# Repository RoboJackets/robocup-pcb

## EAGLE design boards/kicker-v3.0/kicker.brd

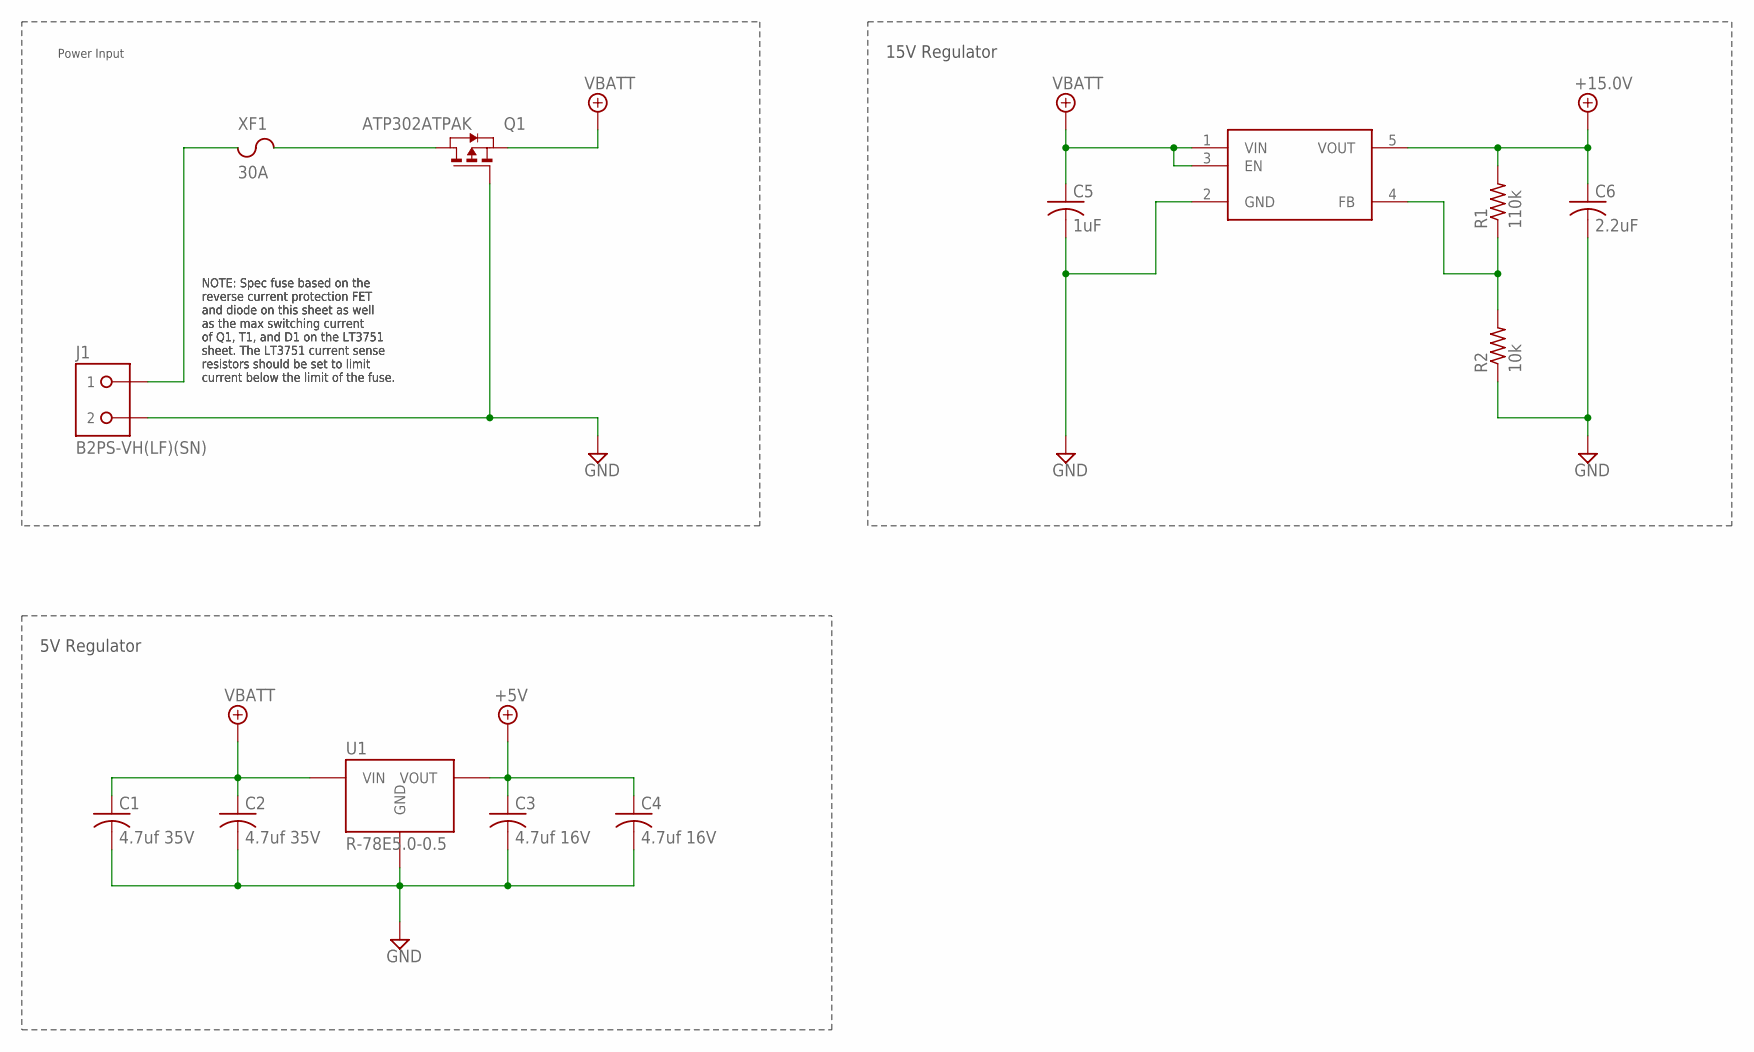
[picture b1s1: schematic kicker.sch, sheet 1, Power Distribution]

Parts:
C1, C2: 4.7uf 35V; C1210
C3, C4: 4.7uf 16V; C1210
C5: 1uF; C0603
C6: 2.2uF; C0603
J1: B2PS-VH(LF)(SN); B2PS-CENTERED
Q1: ATP302ATPAK; TO460P950X150-3
R1: 110k; R0603
R2: 10k; R0603
U1: R-78E5.0-0.5; R-78E
U2: 15V; SOT95P280X145-5
XF1: 30A; 3557-2

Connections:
+5V: C3.1, C4.1, U1.3 (VOUT); also elsewhere on the board
+15.0V: C6.1, R1.2, U2.5 (VOUT); also elsewhere on the board
GND: C1.2, C2.2, C3.2, C4.2, C5.2, C6.2, J1.2, Q1.1 (G), R2.1, U1.2 (GND), U2.2 (GND); also elsewhere on the board
unnamed: Q1.3 (D), XF1.3 (2), XF1.4 (2)
unnamed: R1.1, R2.2, U2.4 (FB)
unnamed: J1.1, XF1.1, XF1.2 (1)
VBATT: C1.1, C2.1, C5.1, Q1.2 (S), U1.1 (VIN), U2.1 (VIN), U2.3 (EN); also elsewhere on the board

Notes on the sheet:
Power Input
5V Regulator
NOTE: Spec fuse based on the reverse current protection FET and diode on this sheet as well as the max switching current of Q1, T1, and D1 on the LT3751 sheet. The LT3751 current sense resistors should be set to limit current below the limit of the fuse.
15V Regulator

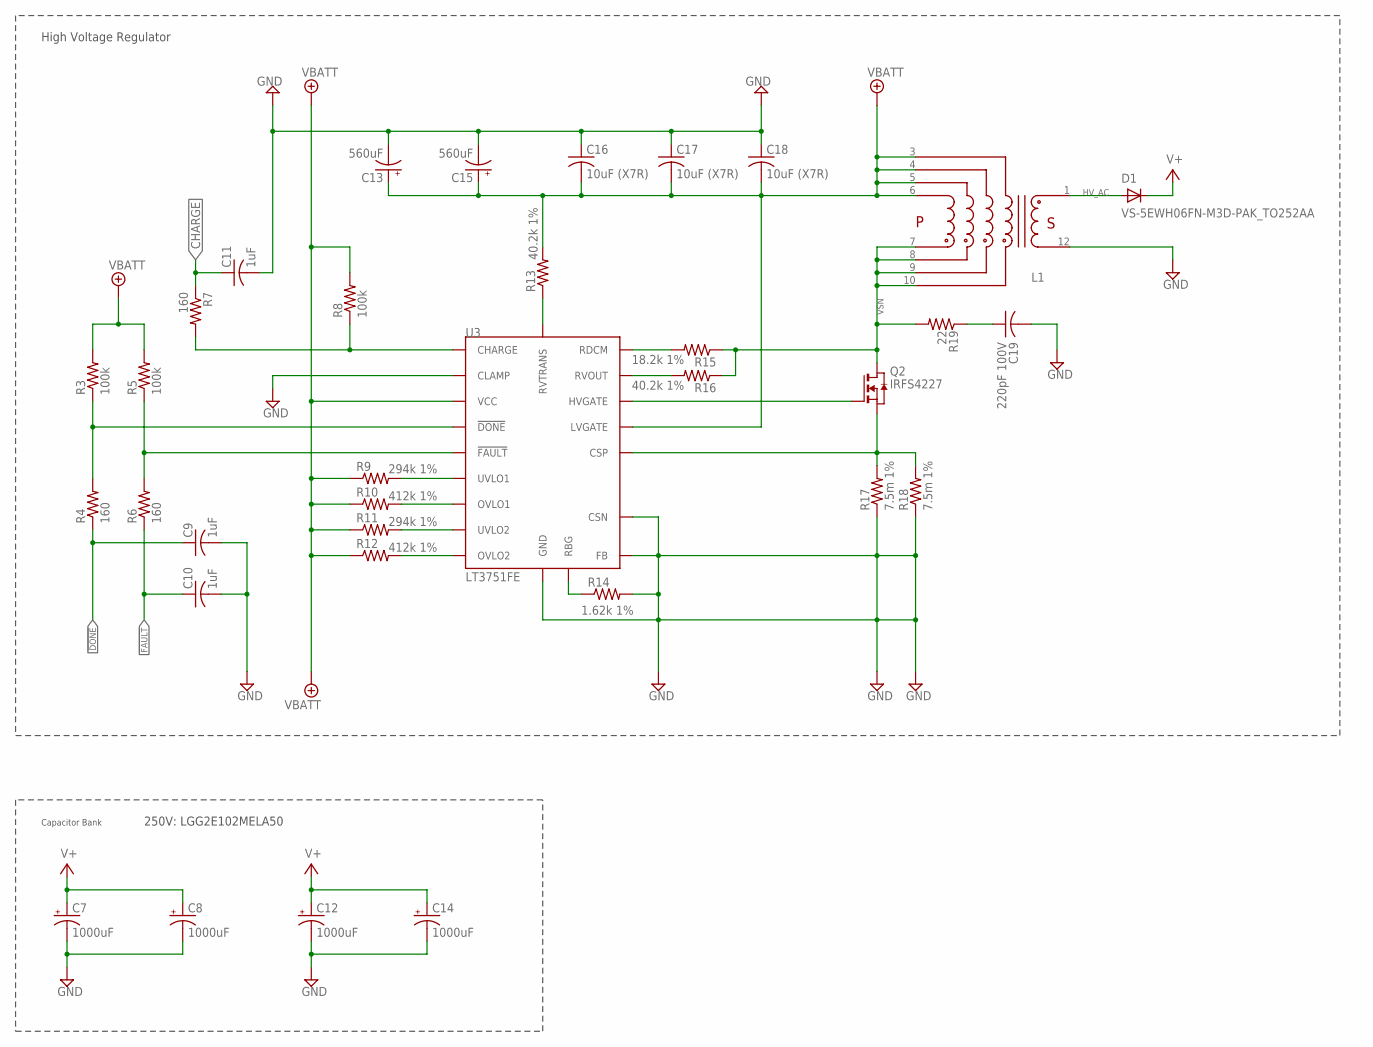
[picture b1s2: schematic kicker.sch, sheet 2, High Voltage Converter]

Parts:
C7, C8, C12, C14: 1000uF; EB25D
C9, C10, C11: 1uF; C0603
C13, C15: 560uF; E7,5-18
C16, C17, C18: 10uF (X7R); C1210
C19: 220pF 100V; C0603
D1: VS-5EWH06FN-M3D-PAK_TO252AA; TO460P990X239-3
L1: GA34XX-BLBL; SOP400P3370X1400-12
Q2: IRFS4227; D2PAK
R3, R5, R8: 100k; R0603
R4, R6, R7: 160; R0603
R9, R11: 294k 1%; R0805
R10, R12: 412k 1%; R0805
R13, R16: 40.2k 1%; R0805
R14: 1.62k 1%; R0805
R15: 18.2k 1%; R0805
R17, R18: 7.5m 1%; R2512
R19: 22; R0805
U3: LT3751FE; TSSOP-20_EP

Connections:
!DONE!: C9.1, R4.1; also elsewhere on the board
!DONE_LPF: R3.1, R4.2, U3.7 (!DONE); also elsewhere on the board
!FAULT!: C10.1, R6.1; also elsewhere on the board
!FAULT_LPF: R5.1, R6.2, U3.6 (!FAULT); also elsewhere on the board
CHARGE: C11.1, R7.1; also elsewhere on the board
CHARGE_LPF: R7.2, R8.1, U3.8 (CHARGE)
GND: C7.-, C8.-, C9.2, C10.2, C11.2, C12.-, C13.-, C14.-, C15.-, C16.1, C17.1, C18.1, C19.2, L1.12, R14.2, R17.1, R18.1, U3.9 (CLAMP), U3.10 (FB), U3.11 (CSN), U3.PAD (GND); also elsewhere on the board
HVGATE: Q2.1 (G), U3.15 (HVGATE)
HV_AC: D1.2 (A), L1.1
unnamed: R14.1, U3.16 (RBG)
unnamed: R13.1, U3.1 (RVTRANS)
unnamed: C19.1, R19.1
OVLO1: R10.2, U3.3 (OVLO1)
OVLO2: R12.2, U3.5 (OVLO2)
RDCM: R15.2, U3.20 (RDCM)
RVOUT: R16.2, U3.18 (RVOUT)
SENSE: Q2.3 (S), R17.2, R18.2, U3.12 (CSP)
UVLO1: R9.2, U3.2 (UVLO1)
UVLO2: R11.2, U3.4 (UVLO2)
V+: C7.+, C8.+, C12.+, C14.+, D1.3 (C); also elsewhere on the board
VBATT: C13.+, C15.+, C16.2, C17.2, C18.2, L1.3, L1.4, L1.5, L1.6, R3.2, R5.2, R8.2, R9.1, R10.1, R11.1, R12.1, R13.2, U3.13 (VCC), U3.14 (LVGATE); also elsewhere on the board
VSN: L1.7, L1.8, L1.9, L1.10, Q2.2 (D), R15.1, R16.1, R19.2

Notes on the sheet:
Capacitor Bank
High Voltage Regulator
250V: LGG2E102MELA50

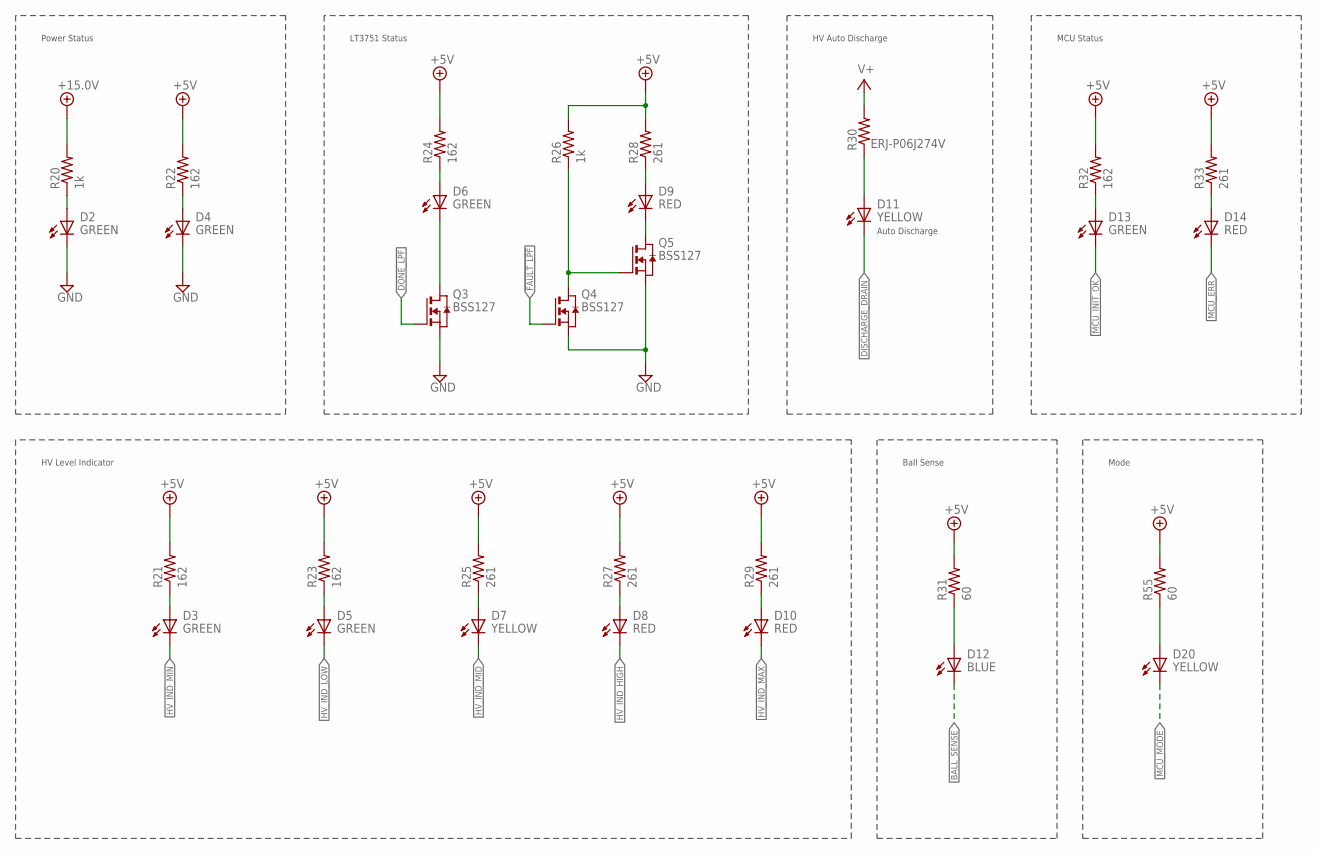
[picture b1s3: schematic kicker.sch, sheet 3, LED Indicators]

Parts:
D2, D3, D4, D5, D6, D13: GREEN; CHIP-LED0603
D7, D11, D20: YELLOW; CHIP-LED0603
D8, D9, D10, D14: RED; CHIP-LED0603
D12: BLUE; CHIP-LED0603
Q3, Q4, Q5: BSS127; SOT-23-3
R20, R26: 1k; R0603
R21, R22, R23, R24, R32: 162; R0603
R25, R27, R28, R29, R33: 261; R0603
R30: ERJ-P06J274V; R0805
R31, R55: 60; R0603

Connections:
!DONE_LPF: Q3.1 (G); also elsewhere on the board
!FAULT_LPF: Q4.1 (G); also elsewhere on the board
+5V: R21.2, R22.2, R23.2, R24.2, R25.2, R26.2, R27.2, R28.2, R29.2, R31.2, R32.2, R33.2, R55.2; also elsewhere on the board
+15.0V: R20.2; also elsewhere on the board
BALL_SENSE: D12.C (K); also elsewhere on the board
DISCHARGE_DRAIN: D11.C (K); also elsewhere on the board
GND: D2.C (K), D4.C (K), Q3.2 (S), Q4.2 (S), Q5.2 (S); also elsewhere on the board
HV_IND_HIGH: D8.C (K); also elsewhere on the board
HV_IND_LOW: D5.C (K); also elsewhere on the board
HV_IND_MAX: D10.C (K); also elsewhere on the board
HV_IND_MID: D7.C (K); also elsewhere on the board
HV_IND_MIN: D3.C (K); also elsewhere on the board
MCU_ERR: D14.C (K); also elsewhere on the board
MCU_INIT_OK: D13.C (K); also elsewhere on the board
MCU_MODE: D20.C (K); also elsewhere on the board
unnamed: D14.A, R33.1
unnamed: D13.A, R32.1
unnamed: D6.A, R24.1
unnamed: D3.A, R21.1
unnamed: D5.A, R23.1
unnamed: D7.A, R25.1
unnamed: D20.A, R55.1
unnamed: D4.A, R22.1
unnamed: D8.A, R27.1
unnamed: D2.A, R20.1
unnamed: Q4.3 (D), Q5.1 (G), R26.1
unnamed: D9.A, R28.1
unnamed: D9.C (K), Q5.3 (D)
unnamed: D11.A, R30.1
unnamed: D10.A, R29.1
unnamed: D6.C (K), Q3.3 (D)
unnamed: D12.A, R31.1
V+: R30.2; also elsewhere on the board

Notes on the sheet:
Power Status
LT3751 Status
Auto Discharge
HV Auto Discharge
MCU Status
HV Level Indicator
Ball Sense
Mode

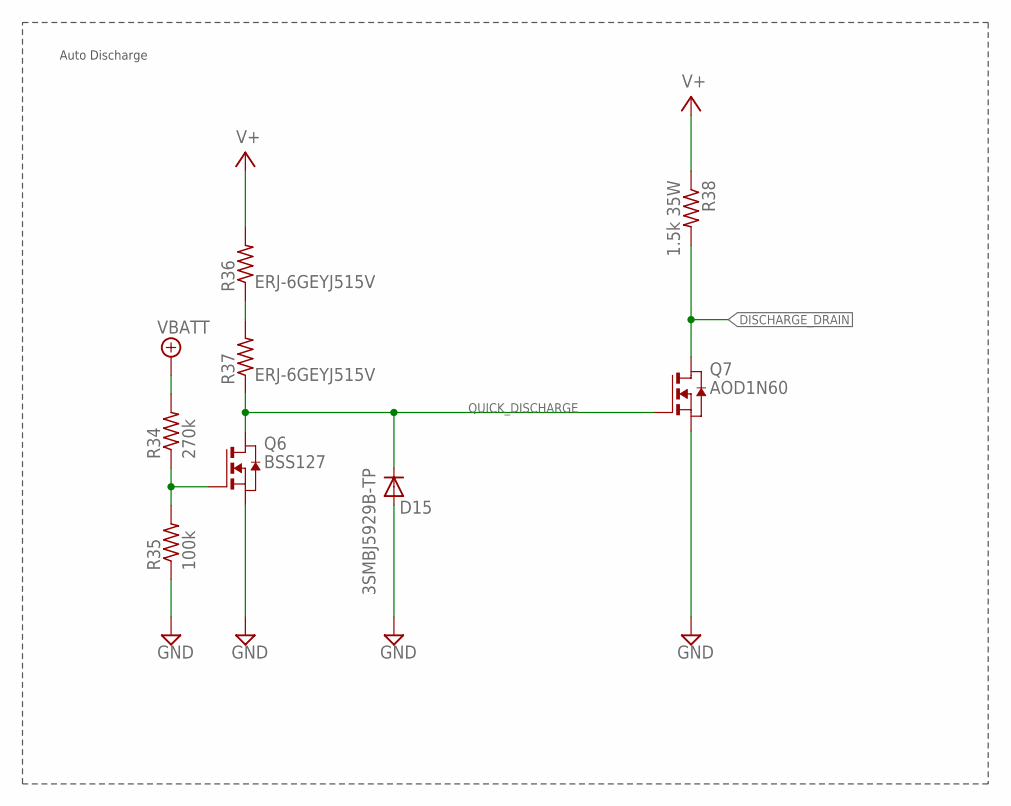
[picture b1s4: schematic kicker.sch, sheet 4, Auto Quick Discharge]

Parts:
D15: 3SMBJ5929B-TP; DO214AA
Q6: BSS127; SOT-23-3
Q7: AOD1N60; DPAK
R34: 270k; R0603
R35: 100k; R0603
R36, R37: ERJ-6GEYJ515V; R0805
R38: 1.5k 35W; TO508P1539X450-3

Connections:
DISCHARGE_DRAIN: Q7.FIN (D), R38.2 (PIN2); also elsewhere on the board
GND: D15.A, Q6.2 (S), Q7.3 (S), R35.1; also elsewhere on the board
unnamed: R36.1, R37.2
unnamed: Q6.1 (G), R34.1, R35.2
QUICK_DISCHARGE: D15.C, Q6.3 (D), Q7.1 (G), R37.1
V+: R36.2, R38.1 (PIN1); also elsewhere on the board
VBATT: R34.2; also elsewhere on the board

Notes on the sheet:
Auto Discharge

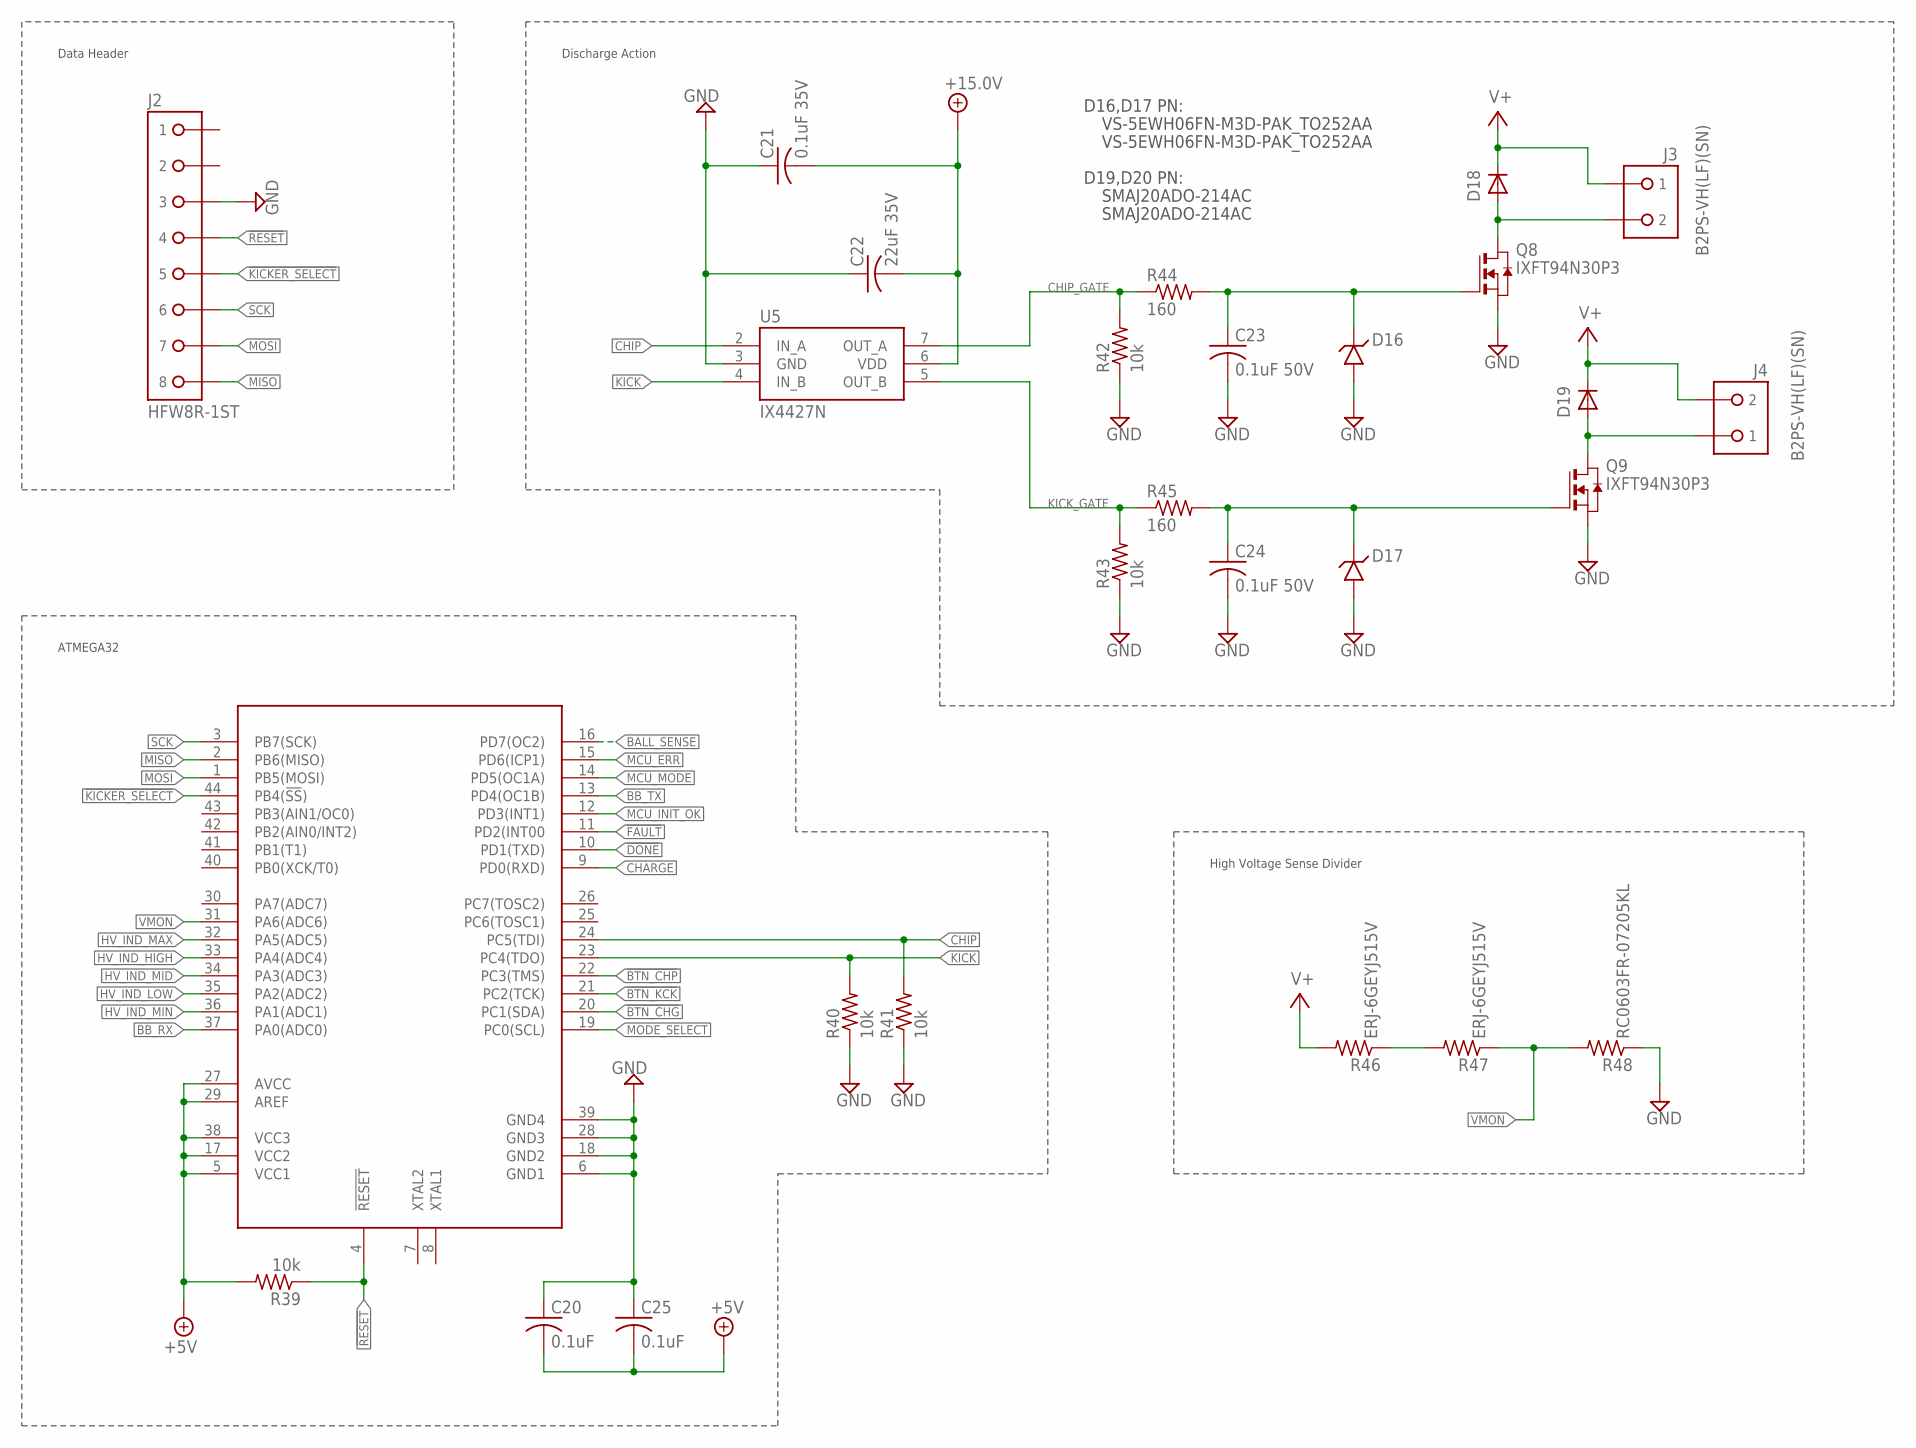
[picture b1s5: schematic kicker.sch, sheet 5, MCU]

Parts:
C20, C25: 0.1uF; C0603
C21: 0.1uF 35V; C0603
C22: 22uF 35V; C0805
C23, C24: 0.1uF 50V; C0603
D16, D17: SMAJ20ADO-214AC; RESM5226X262
D18, D19: VS-5EWH06FN-M3D-PAK_TO252AA; TO460P990X239-3
J2: HFW8R-1ST
J3, J4: B2PS-VH(LF)(SN); B2PS-CENTERED
Q8, Q9: IXFT94N30P3; TO-268
R39, R40, R41, R42, R43: 10k; R0603
R44, R45: 160; R1206
R46, R47: ERJ-6GEYJ515V; R0805
R48: RC0603FR-07205KL; R0603
U4: AT32ATQFP44; QFP80P1200X1200X120-44
U5: IX4427N; SOIC-8

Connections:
!BTN_CHG: U4.20 (PC1(SDA)); also elsewhere on the board
!BTN_CHP: U4.22 (PC3(TMS)); also elsewhere on the board
!BTN_KCK: U4.21 (PC2(TCK)); also elsewhere on the board
!DONE!: U4.10 (PD1(TXD)); also elsewhere on the board
!FAULT!: U4.11 (PD2(INT00); also elsewhere on the board
!KICKER_SELECT: J2.5, U4.44 (PB4(!SS!))
!RESET: J2.4, R39.1, U4.4 (!RESET!)
+5V: C20.2, C25.2, R39.2, U4.5 (VCC1), U4.17 (VCC2), U4.27 (AVCC), U4.29 (AREF), U4.38 (VCC3); also elsewhere on the board
+15.0V: C21.2, C22.2, U5.6 (VDD); also elsewhere on the board
BALL_SENSE: U4.16 (PD7(OC2)); also elsewhere on the board
BB_RX: U4.37 (PA0(ADC0)); also elsewhere on the board
BB_TX: U4.13 (PD4(OC1B)); also elsewhere on the board
CHARGE: U4.9 (PD0(RXD)); also elsewhere on the board
CHIP: R41.2, U4.24 (PC5(TDI)), U5.2 (IN_A)
CHIPPER: D18.2 (A), J3.2, Q8.4 (D)
CHIP_GATE: R42.2, R44.1, U5.7 (OUT_A)
GND: C20.1, C21.1, C22.1, C23.2, C24.2, C25.1, D16.1 (A), D17.1 (A), J2.3, Q8.3 (S), Q9.3 (S), R40.1, R41.1, R42.1, R43.1, R48.1, U4.6 (GND1), U4.18 (GND2), U4.28 (GND3), U4.39 (GND4), U5.3 (GND); also elsewhere on the board
HV_IND_HIGH: U4.33 (PA4(ADC4)); also elsewhere on the board
HV_IND_LOW: U4.35 (PA2(ADC2)); also elsewhere on the board
HV_IND_MAX: U4.32 (PA5(ADC5)); also elsewhere on the board
HV_IND_MID: U4.34 (PA3(ADC3)); also elsewhere on the board
HV_IND_MIN: U4.36 (PA1(ADC1)); also elsewhere on the board
KICK: R40.2, U4.23 (PC4(TDO)), U5.4 (IN_B)
KICKER: D19.2 (A), J4.1, Q9.4 (D)
KICK_GATE: R43.2, R45.1, U5.5 (OUT_B)
MCU_ERR: U4.15 (PD6(ICP1)); also elsewhere on the board
MCU_INIT_OK: U4.12 (PD3(INT1)); also elsewhere on the board
MCU_MODE: U4.14 (PD5(OC1A)); also elsewhere on the board
MISO: J2.8, U4.2 (PB6(MISO))
MODE_SELECT: U4.19 (PC0(SCL)); also elsewhere on the board
MOSI: J2.7, U4.1 (PB5(MOSI))
unnamed: C23.1, D16.2 (C), Q8.1 (G), R44.2
unnamed: C24.1, D17.2 (C), Q9.1 (G), R45.2
unnamed: R46.1, R47.2
SCK: J2.6, U4.3 (PB7(SCK))
V+: D18.3 (C), D19.3 (C), J3.1, J4.2, R46.2; also elsewhere on the board
VMON: R47.1, R48.2, U4.31 (PA6(ADC6))

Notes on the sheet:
ATMEGA32
Data Header
Discharge Action
High Voltage Sense Divider
D16,D17 PN:
D19,D20 PN:
VS-5EWH06FN-M3D-PAK_TO252AA
SMAJ20ADO-214AC

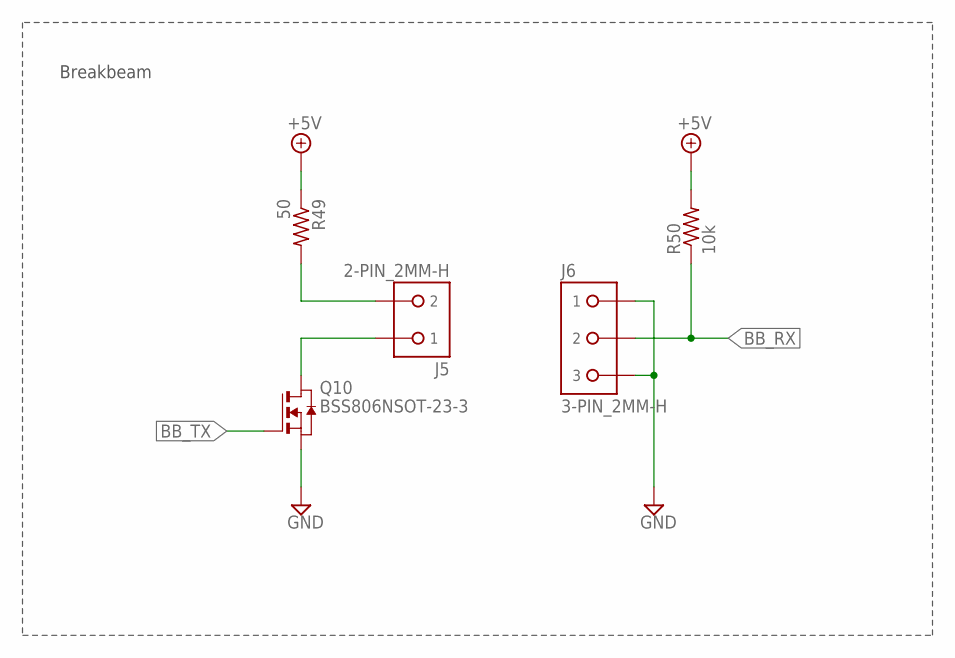
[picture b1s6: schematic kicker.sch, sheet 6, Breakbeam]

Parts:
J5: 2-PIN_2MM-H; 2MM-2-H
J6: 3-PIN_2MM-H; 2MM-3-H
Q10: BSS806NSOT-23-3; SOT95P240X110-3
R49: 50; R0603
R50: 10k; R0603

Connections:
+5V: R49.1, R50.2; also elsewhere on the board
BB_RX: J6.2, R50.1; also elsewhere on the board
BB_TX: Q10.1 (G); also elsewhere on the board
GND: J6.1, J6.3, Q10.2 (S); also elsewhere on the board
unnamed: J5.2, R49.2
unnamed: J5.1, Q10.3 (D)

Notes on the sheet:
Breakbeam

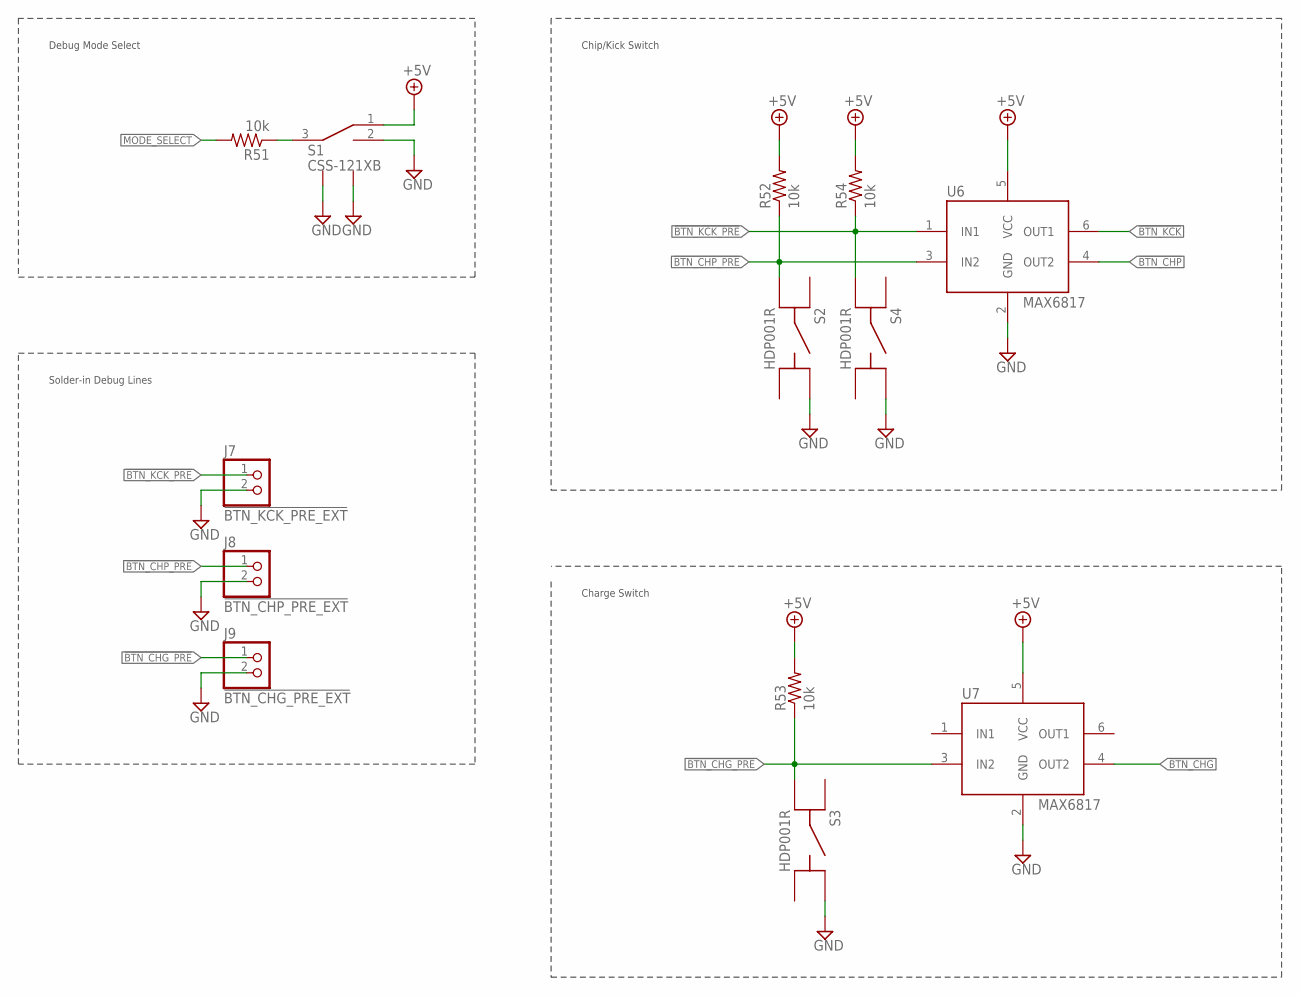
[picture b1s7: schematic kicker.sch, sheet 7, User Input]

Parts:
J7: !BTN_KCK_PRE_EXT; 1X2
J8: !BTN_CHP_PRE_EXT; 1X2
J9: !BTN_CHG_PRE_EXT; 1X2
R51, R52, R53, R54: 10k; R0603
S1: CSS-121XB
S2, S3, S4: HDP001R
U6, U7: MAX6817; SOT-23-6

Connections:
!BTN_CHG: U7.4 (OUT2); also elsewhere on the board
!BTN_CHG_PRE: J9.1, R53.1, S3.C (A2), U7.3 (IN2)
!BTN_CHP: U6.4 (OUT2); also elsewhere on the board
!BTN_CHP_PRE: J8.1, R52.1, S2.C (A2), U6.3 (IN2)
!BTN_KCK: U6.6 (OUT1); also elsewhere on the board
!BTN_KCK_PRE: J7.1, R54.1, S4.C (A2), U6.1 (IN1)
+5V: R52.2, R53.2, R54.2, S1.1 (A), U6.5 (VCC), U7.5 (VCC); also elsewhere on the board
GND: J7.2, J8.2, J9.2, S1.2 (B), S1.LEG1, S1.LEG4 (LEG2), S2.B (B1), S3.B (B1), S4.B (B1), U6.2 (GND), U7.2 (GND); also elsewhere on the board
MODE_SELECT: R51.2; also elsewhere on the board
unnamed: R51.1, S1.3 (COMMON)

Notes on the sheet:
Debug Mode Select
Chip/Kick Switch
Charge Switch
Solder-in Debug Lines

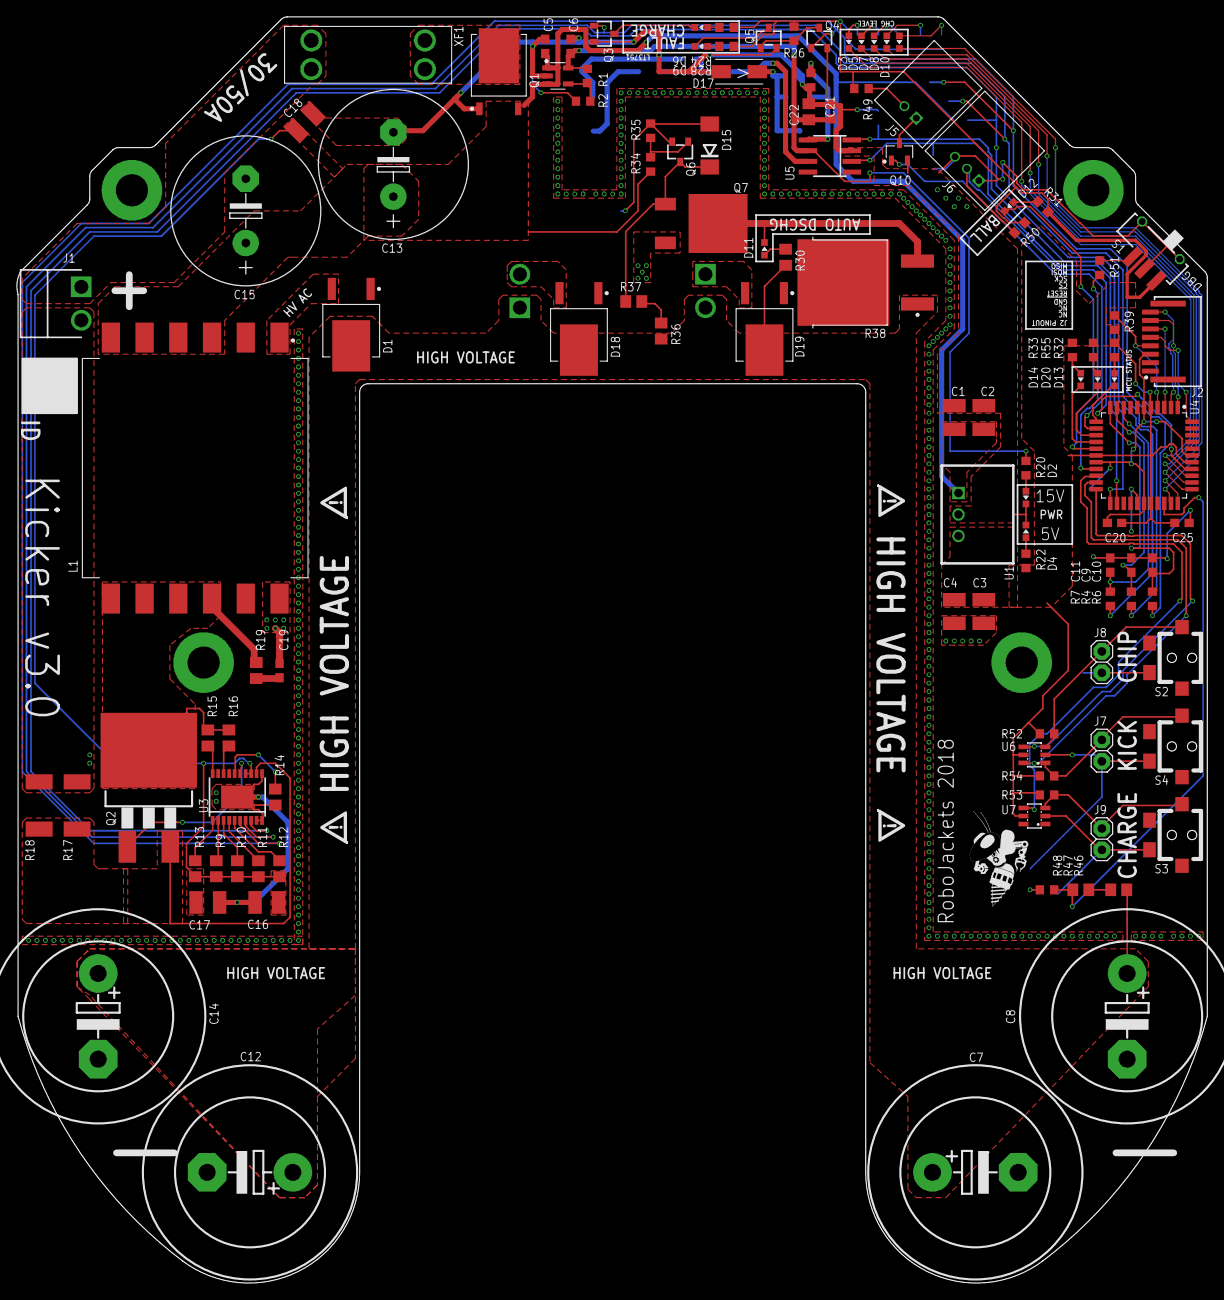
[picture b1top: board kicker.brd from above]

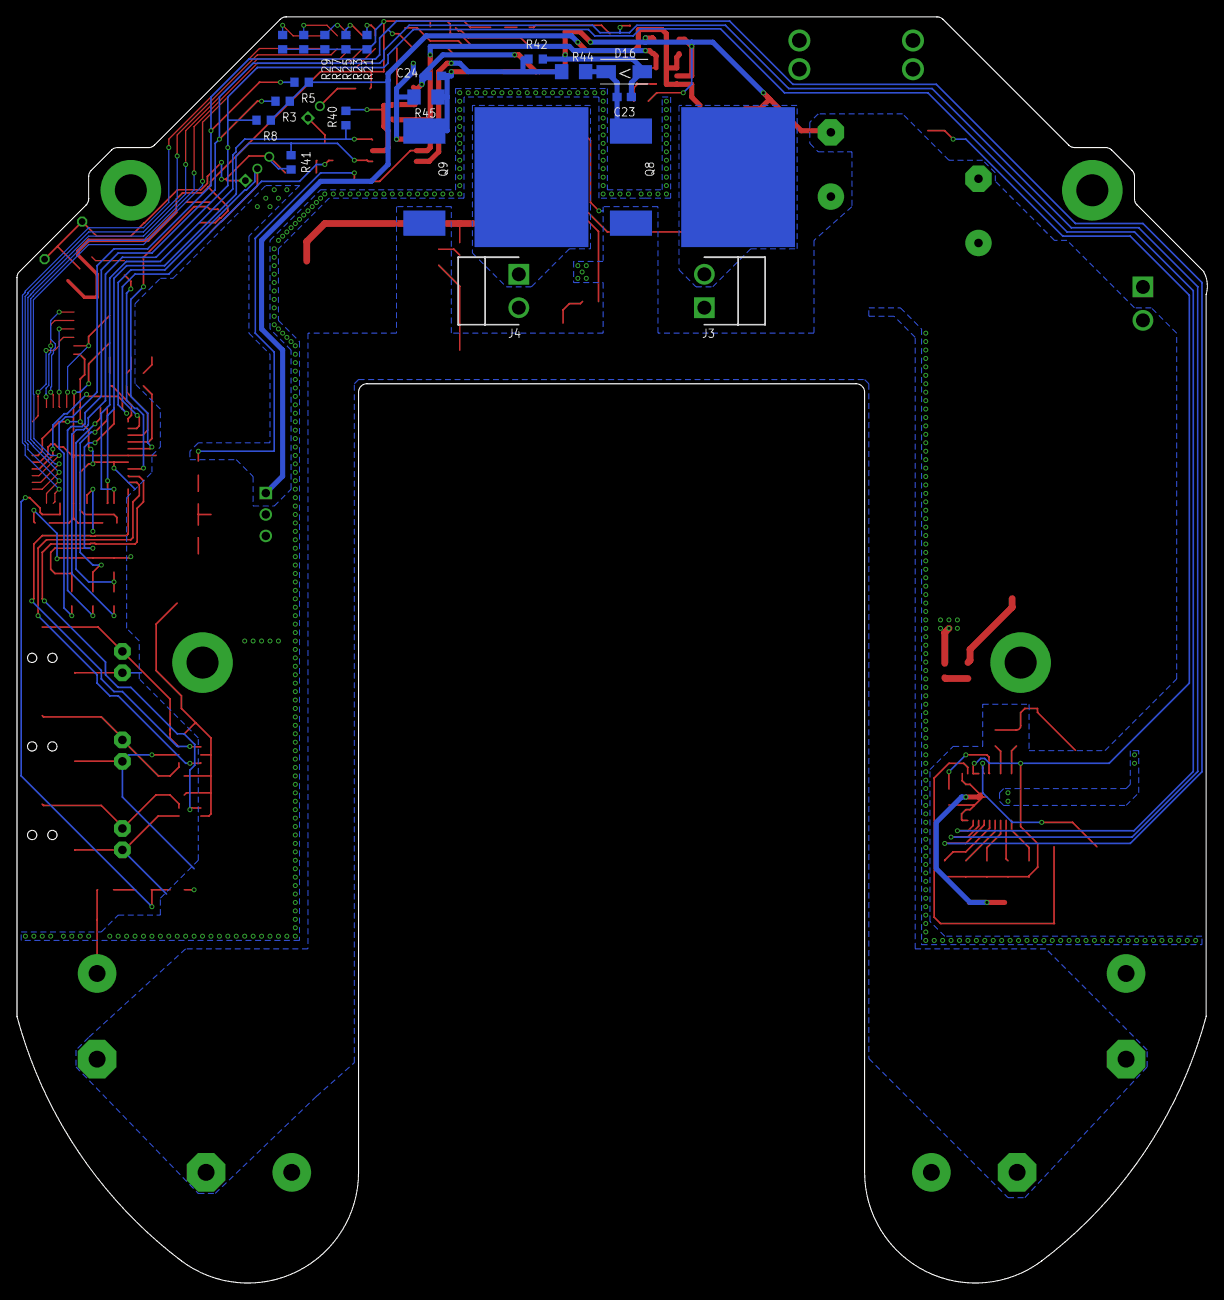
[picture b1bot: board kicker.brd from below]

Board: 2 copper layers, 141.1 x 150.1 mm, 137 parts (20 on the bottom side), 84 nets.

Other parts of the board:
U$1, U$2, U$3, U$4: WARNING2
U$5: ROBOBUZZ_0.6X

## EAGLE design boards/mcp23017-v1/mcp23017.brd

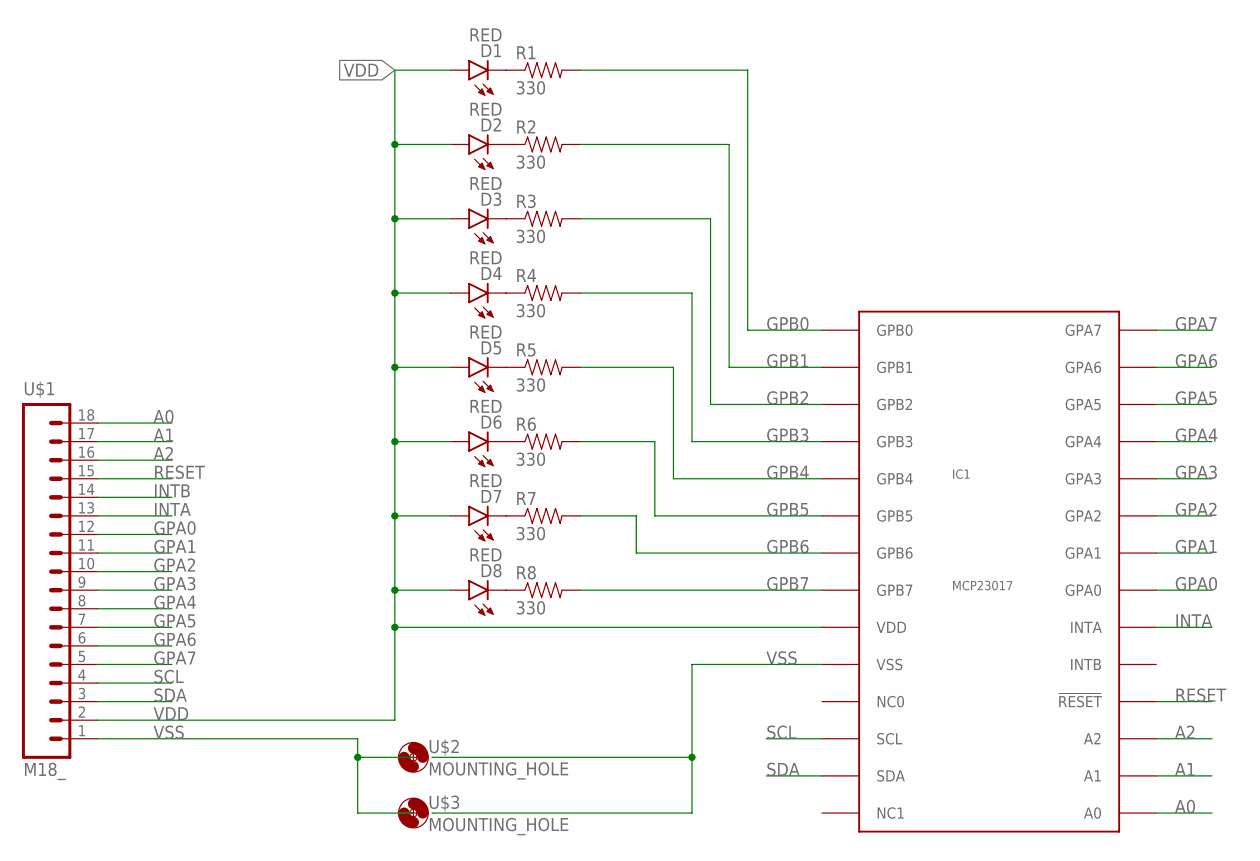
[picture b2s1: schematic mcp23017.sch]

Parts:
D1, D2, D3, D4, D5, D6, D7, D8: RED; LED-0603
IC1: MCP23017; SSOP-28
R1, R2, R3, R4, R5, R6, R7, R8: 330; 0603-RES
U$1: M18_; 1X18
U$2, U$3: MOUNTING_HOLE

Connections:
A0: IC1.15 (A0), U$1.18
A1: IC1.16 (A1), U$1.17
A2: IC1.17 (A2), U$1.16
GPA0: IC1.21 (GPA0), U$1.12
GPA1: IC1.22 (GPA1), U$1.11
GPA2: IC1.23 (GPA2), U$1.10
GPA3: IC1.24 (GPA3), U$1.9
GPA4: IC1.25 (GPA4), U$1.8
GPA5: IC1.26 (GPA5), U$1.7
GPA6: IC1.27 (GPA6), U$1.6
GPA7: IC1.28 (GPA7), U$1.5
GPB0: IC1.1 (GPB0), R1.2
GPB1: IC1.2 (GPB1), R2.2
GPB2: IC1.3 (GPB2), R3.2
GPB3: IC1.4 (GPB3), R4.2
GPB4: IC1.5 (GPB4), R5.2
GPB5: IC1.6 (GPB5), R6.2
GPB6: IC1.7 (GPB6), R7.2
GPB7: IC1.8 (GPB7), R8.2
INTA: IC1.20 (INTA), U$1.13
INTB: U$1.14
unnamed: D1.C, R1.1
unnamed: D2.C, R2.1
unnamed: D3.C, R3.1
unnamed: D4.C, R4.1
unnamed: D5.C, R5.1
unnamed: D6.C, R6.1
unnamed: D7.C, R7.1
unnamed: D8.C, R8.1
RESET: IC1.18 (!RESET!), U$1.15
SCL: IC1.12 (SCL), U$1.4
SDA: IC1.13 (SDA), U$1.3
VDD: D1.A, D2.A, D3.A, D4.A, D5.A, D6.A, D7.A, D8.A, IC1.9 (VDD), U$1.2
VSS: IC1.10 (VSS), U$1.1, U$2.GND, U$3.GND

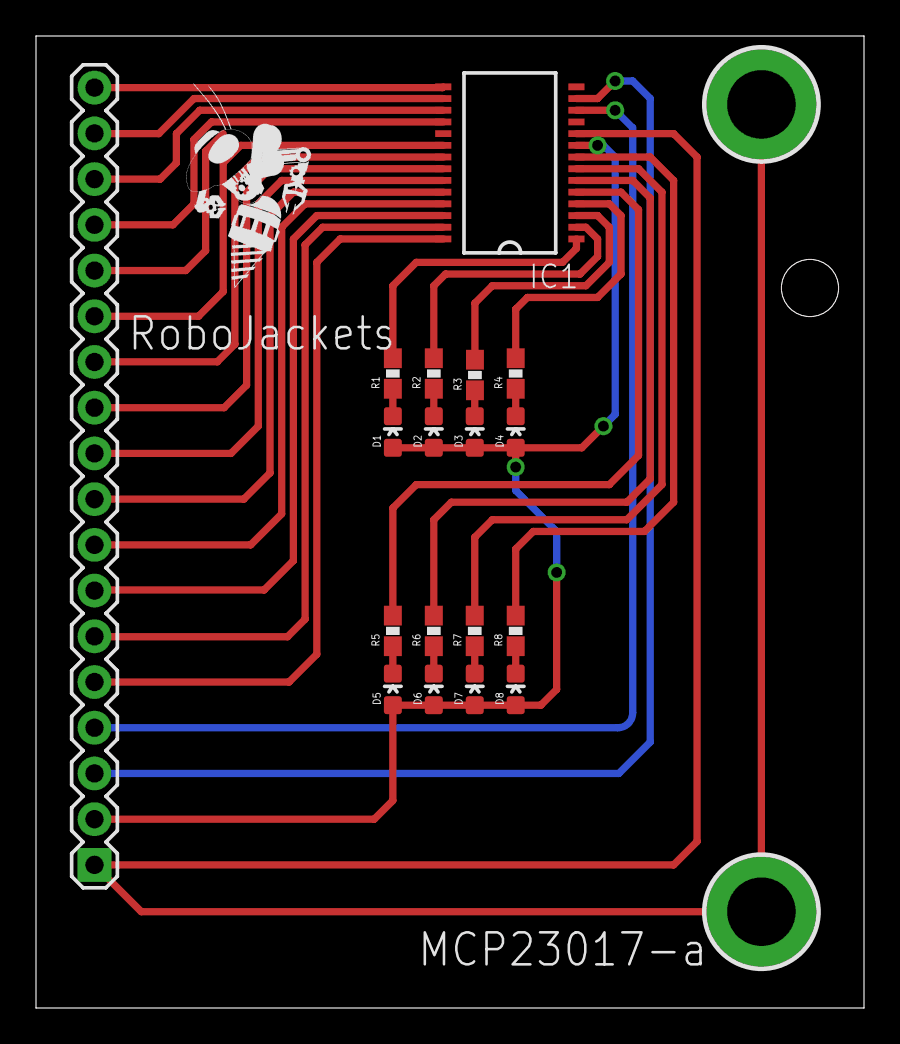
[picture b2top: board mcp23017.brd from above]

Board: 2 copper layers, 46.0 x 54.0 mm, 21 parts (0 on the bottom side), 33 nets.

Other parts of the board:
U$4: ROBOBUZZ_0.6X

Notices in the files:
parts and their libraries:
SparkFun-Connectors: Licensing: Creative Commons ShareAlike 4.0 International - https://creativecommons.org/licenses/by-sa/4.0
